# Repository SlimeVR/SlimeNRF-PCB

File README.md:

## notes

You need a segger jlink programmer to use this, USB dfu does not come with the initial bootloader of isp, and nrf52832 has no USB connectivity. nRF52840-dk development kit can be used, and also can double as a dongle for the trackers.

# slimenrf r3

Revision 3

E73-2G4M08S1C (nrf52840), icm42688 or compatible, mmc5983ma

https://oshwlab.com/sctanf/slimenrf3

# slimenrfaux2

Revision 2

isp1507-ax (nrf52832), icm42688 or compatible, mmc5983ma

* Uses nrf52832, no USB, SWD pins on dock connector instead
* No 0201 parts
* Removed onboard charger
* LED is brighter (sink instead of source)

pcb|3d
--|--
|

pcb before reflow|pcb with battery|tracker and case ()
--|--|--
||

# slimenrfauxaux2

Revision 2

icm42688 or compatible, mmc5983ma

pcb|3d
--|--
|

# slimenrfaux

Revision 1

isp1807-lr (nrf52840), icm42688 or compatible, mmc5983ma

* USB untested
* 0201 components are hard to solder
* Charger is hard to solder
* LED with default resistor is too dim

pcb|3d
--|--
|

finished pcb|pcb with battery|completed tracker (case: )
--|--|--
||

# slimenrfauxaux

Revision 1

icm42688 or compatible, mmc5983ma

* 0201 components are hard to solder

pcb|3d
--|--
|

# slimenrfdock

dock test pcb

charging for 8 devices at 300mA, max power draw 2.4A

* Gets pretty hot if all 8 chargers are in use but it works fine

pcb|3d
--|--
|

completed charger pcb|charging dock ()
--|--
|

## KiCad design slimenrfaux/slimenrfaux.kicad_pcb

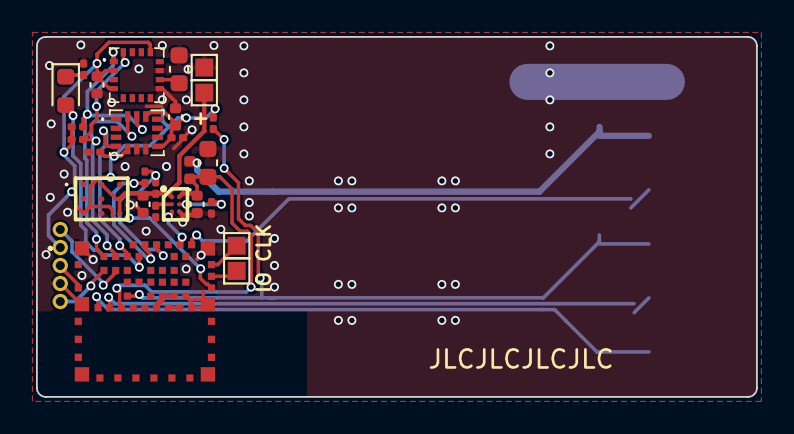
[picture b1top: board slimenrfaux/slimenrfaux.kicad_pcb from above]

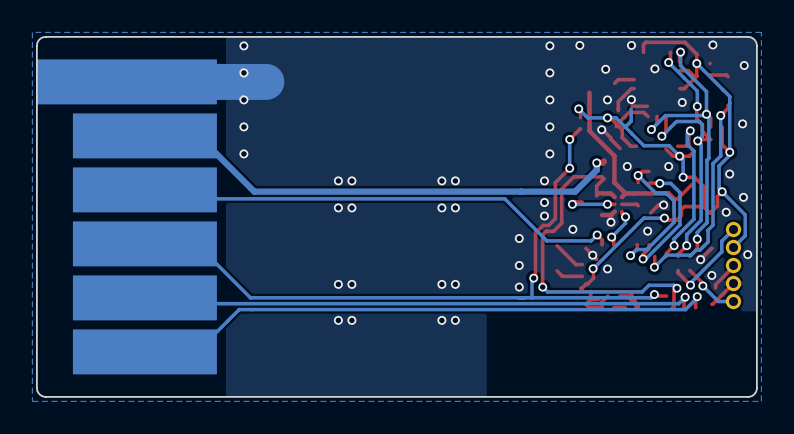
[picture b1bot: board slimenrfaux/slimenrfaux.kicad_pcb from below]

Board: 2 copper layers, 40.0 x 20.0 mm, 34 parts (6 on the bottom side), 26 nets.

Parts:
AC2: ICM-42688-V; IIM42352
C3, C4, C12: 1uF; C_0402_1005Metric
C8: 4.7uF; C_0603_1608Metric
C9: 10nF; C_0201_0603Metric
C10: 0.1uF; C_0201_0603Metric
C11: 2.2uF; C_0402_1005Metric
C13: 10uF; C_0603_1608Metric
D1: LED; LED_0603_1608Metric
D2: D; D_0402_1005Metric
IC1: ISP1807-LR-RS; ISP1807LRRS
IC2: BQ25101YFPR; BGA6C40P2X3_88X158X50
IC3: MMC5983MA
J1: Conn_01x05_Male; PinHeader_1x05_P1.00mm_Horizontal
PS1: TPS82740ASIPR
R1, R10: 10K; R_0201_0603Metric
R2: 540; R_0201_0603Metric
R4, R5: 2.7K; R_0201_0603Metric
R7: 1M; R_0201_0603Metric
R8: 510K; R_0201_0603Metric
R9: 10; R_0201_0603Metric
TP1, TP2, TP3, TP4, TP5, TP6, TP7, TP8, TP9, TP10: TestPoint; TestPoint_Pad_1.0x1.0mm

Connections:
ADCBAT: IC1.38 (P0_03_AIN1), R7.2, R8.1
ADCBATEN: IC1.40 (P0_02_AIN0), R8.2
CHGSTAT: IC1.34 (P0_06), IC2.C1 (~CHG)
D+: IC1.8 (D+), TP8.1
D-: IC1.10 (D-), TP7.1
Dock: IC1.32 (P0_08), TP5.1
GND: AC2.1 (AP_SDO_/_AP_AD0), AC2.6 (GND), AC2.7 (RESV_3), AC2.9 (INT2_/_FSYNC_/_CLKIN), C3.1, C4.2, C8.2, C9.2, C10.2, C11.2, C12.2, C13.2, IC1.1 (VSS_1), IC1.7 (VSS_2), IC1.14 (VSS_3), IC1.16 (VSS_4), IC1.18 (VSS_5), IC1.19 (P0_24), IC1.21 (VSS_6), IC1.23 (VSS_7), IC1.24 (VSS_8), IC1.25 (VSS_9), IC1.31 (VSS_10), IC2.C2 (VSS), IC3.9 (GND_1), IC3.11 (GND_2), J1.2, PS1.A1 (VSEL3), PS1.A3 (VSEL1), PS1.C2 (GND), R1.1, R2.2, R9.2, TP2.1, TP3.1
INT: AC2.4 (INT1_/_INT), IC1.43 (P0_11_TRACEDATA2)
INT2: IC1.6 (P0_26), J1.3
LED: D1.2 (A), IC1.41 (P0_25)
unnamed: C13.1, IC3.10 (CAP)
unnamed: D2.2 (A), TP4.1
unnamed: IC1.20 (OUT_ANT), IC1.22 (OUT_MOD)
unnamed: IC2.B1 (TS), R1.2
unnamed: IC2.B2 (ISET), R2.1
unnamed: D1.1 (K), R9.1
RST: IC1.13 (P0_18_RESET), R10.2, TP6.1
SCL: AC2.13 (AP_SCL_/_AP_SCLK), IC1.47 (P0_23), IC3.1 (SCL/SPI_SCK), R5.2
SCLAUX: IC1.56 (P1_09_TRACEDATA3), J1.1
SDA: AC2.14 (AP_SDA_/_AP_SDIO_/_AP_SDI), IC1.45 (P0_19), IC3.16 (SDA/SPI_SDI), R4.2
SDAAUX: IC1.55 (P1_08), J1.5
SWDCLK: IC1.30 (SWDCLK), TP10.1
SWDIO: IC1.28 (SWDIO), TP9.1
VBAT: C3.2, IC2.A1 (OUT), PS1.A2 (VSEL2), PS1.B3 (EN), PS1.C3 (VIN), R7.1, TP1.1
VBUS: C4.1, C8.1, D2.1 (K), IC1.12 (VBUS), IC2.A2 (IN)
VDD: AC2.5 (VDDIO), AC2.8 (VDD), AC2.12 (AP_CS), C9.1, C10.1, C11.1, C12.1, IC1.26 (VCC_NRF), IC3.2 (VDD), IC3.4 (SPI_CS), IC3.13 (VDDIO), J1.4, PS1.C1 (VOUT), R4.1, R5.1, R10.1

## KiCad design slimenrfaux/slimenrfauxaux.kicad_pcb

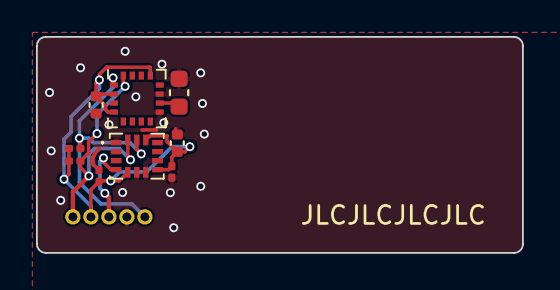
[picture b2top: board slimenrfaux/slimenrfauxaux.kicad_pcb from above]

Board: 2 copper layers, 27.0 x 12.0 mm, 10 parts (0 on the bottom side), 6 nets.

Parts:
AC2: ICM-42688-V; IIM42352
C9: 10nF; C_0201_0603Metric
C10: 0.1uF; C_0201_0603Metric
C11: 2.2uF; C_0402_1005Metric
C12: 1uF; C_0402_1005Metric
C13: 10uF; C_0603_1608Metric
J1: Conn_01x05_Male; PinHeader_1x05_P1.00mm_Horizontal
R4, R5: 2.2K; R_0201_0603Metric
U1: MMC5883MA; LGA-16_3x3mm_P0.5mm

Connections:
GND: AC2.1 (AP_SDO_/_AP_AD0), AC2.6 (GND), AC2.7 (RESV_3), AC2.9 (INT2_/_FSYNC_/_CLKIN), C9.2, C10.2, C11.2, C12.2, C13.2, J1.2, U1.9 (GND), U1.11 (GND)
INT: AC2.4 (INT1_/_INT), J1.3
unnamed: C13.1, U1.10 (CAP)
SCL: AC2.13 (AP_SCL_/_AP_SCLK), J1.1, R5.2, U1.1 (SCL)
SDA: AC2.14 (AP_SDA_/_AP_SDIO_/_AP_SDI), J1.5, R4.2, U1.16 (SDA)
VDD: AC2.5 (VDDIO), AC2.8 (VDD), AC2.12 (AP_CS), C9.1, C10.1, C11.1, C12.1, J1.4, R4.1, R5.1, U1.2 (VDD), U1.4 (NC), U1.13 (VDDIO)

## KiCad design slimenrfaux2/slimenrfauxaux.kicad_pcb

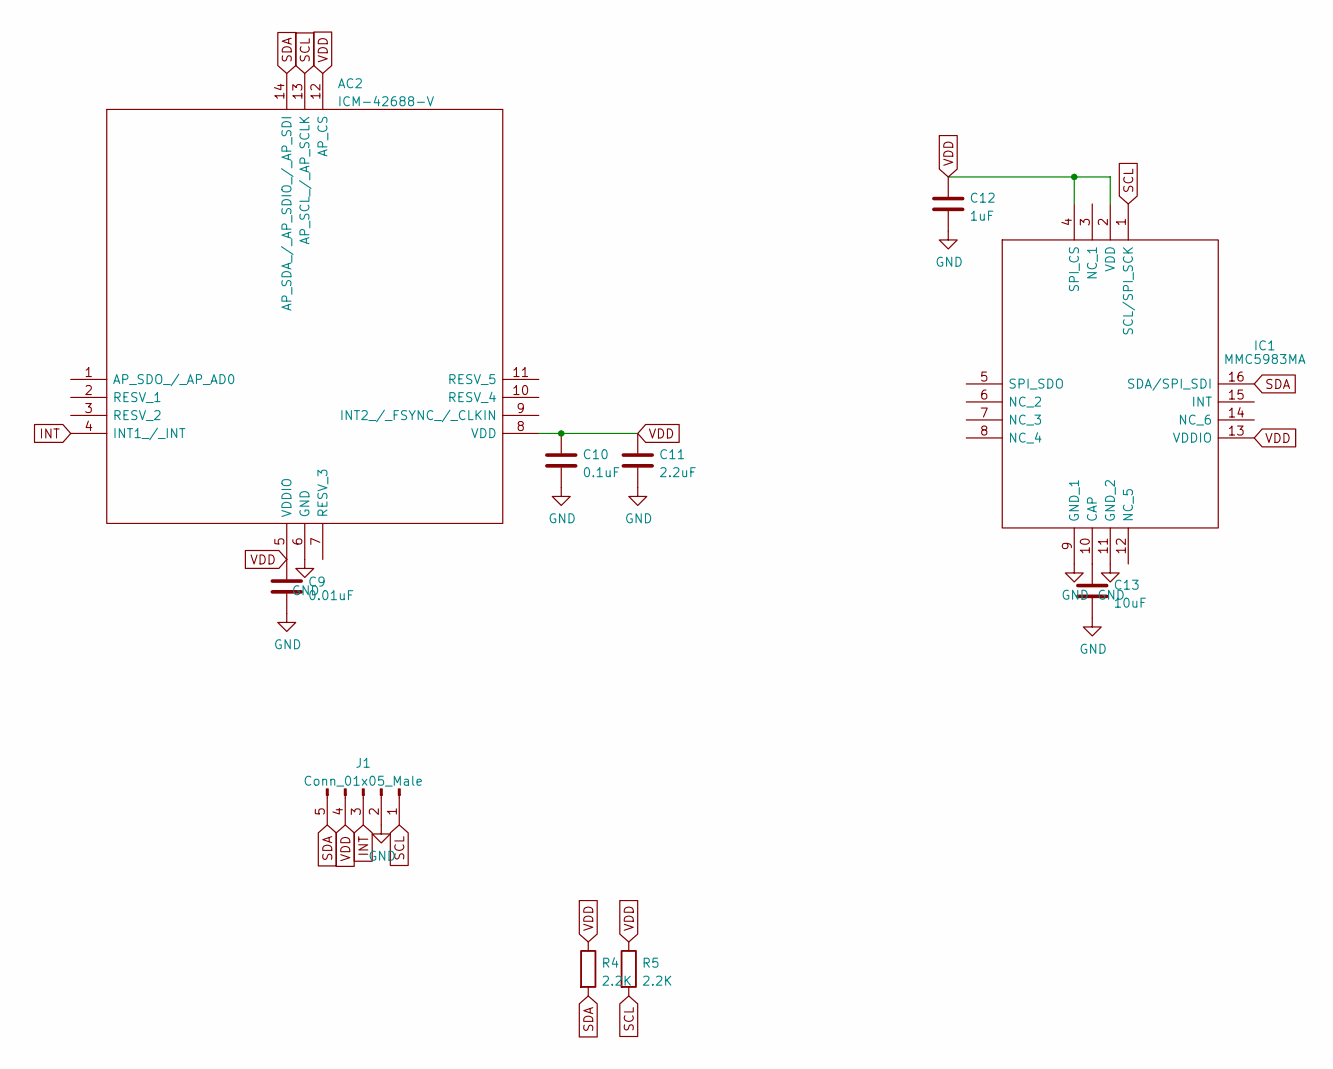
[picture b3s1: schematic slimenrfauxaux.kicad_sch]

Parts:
AC2: ICM-42688-V; IIM42352; Mouser Part Number 410-ICM-42688-V
C9: 0.01uF; C_0402_1005Metric
C10: 0.1uF; C_0402_1005Metric
C11: 2.2uF; C_0402_1005Metric
C12: 1uF; C_0402_1005Metric
C13: 10uF; C_0603_1608Metric
IC1: MMC5983MA; Mouser Part Number 438-MMC5983MA
J1: Conn_01x05_Male; PinHeader_1x05_P1.00mm_Horizontal
R4, R5: 2.2K; R_0402_1005Metric

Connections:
GND: AC2.6 (GND), C9.2, C10.2, C11.2, C12.2, C13.2, IC1.9 (GND_1), IC1.11 (GND_2), J1.2
INT: AC2.4 (INT1_/_INT), J1.3
unnamed: C13.1, IC1.10 (CAP)
SCL: AC2.13 (AP_SCL_/_AP_SCLK), IC1.1 (SCL/SPI_SCK), J1.1, R5.2
SDA: AC2.14 (AP_SDA_/_AP_SDIO_/_AP_SDI), IC1.16 (SDA/SPI_SDI), J1.5, R4.2
VDD: AC2.5 (VDDIO), AC2.8 (VDD), AC2.12 (AP_CS), C9.1, C10.1, C11.1, C12.1, IC1.2 (VDD), IC1.4 (SPI_CS), IC1.13 (VDDIO), J1.4, R4.1, R5.1

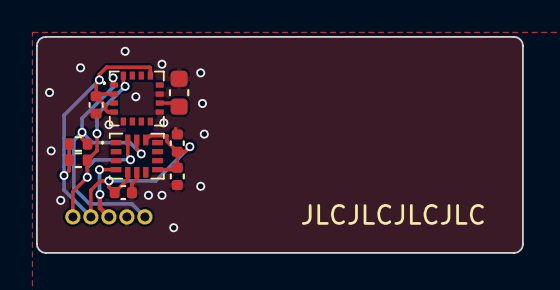
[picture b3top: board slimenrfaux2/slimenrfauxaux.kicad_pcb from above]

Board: 2 copper layers, 27.0 x 12.0 mm, 10 parts (0 on the bottom side), 6 nets.

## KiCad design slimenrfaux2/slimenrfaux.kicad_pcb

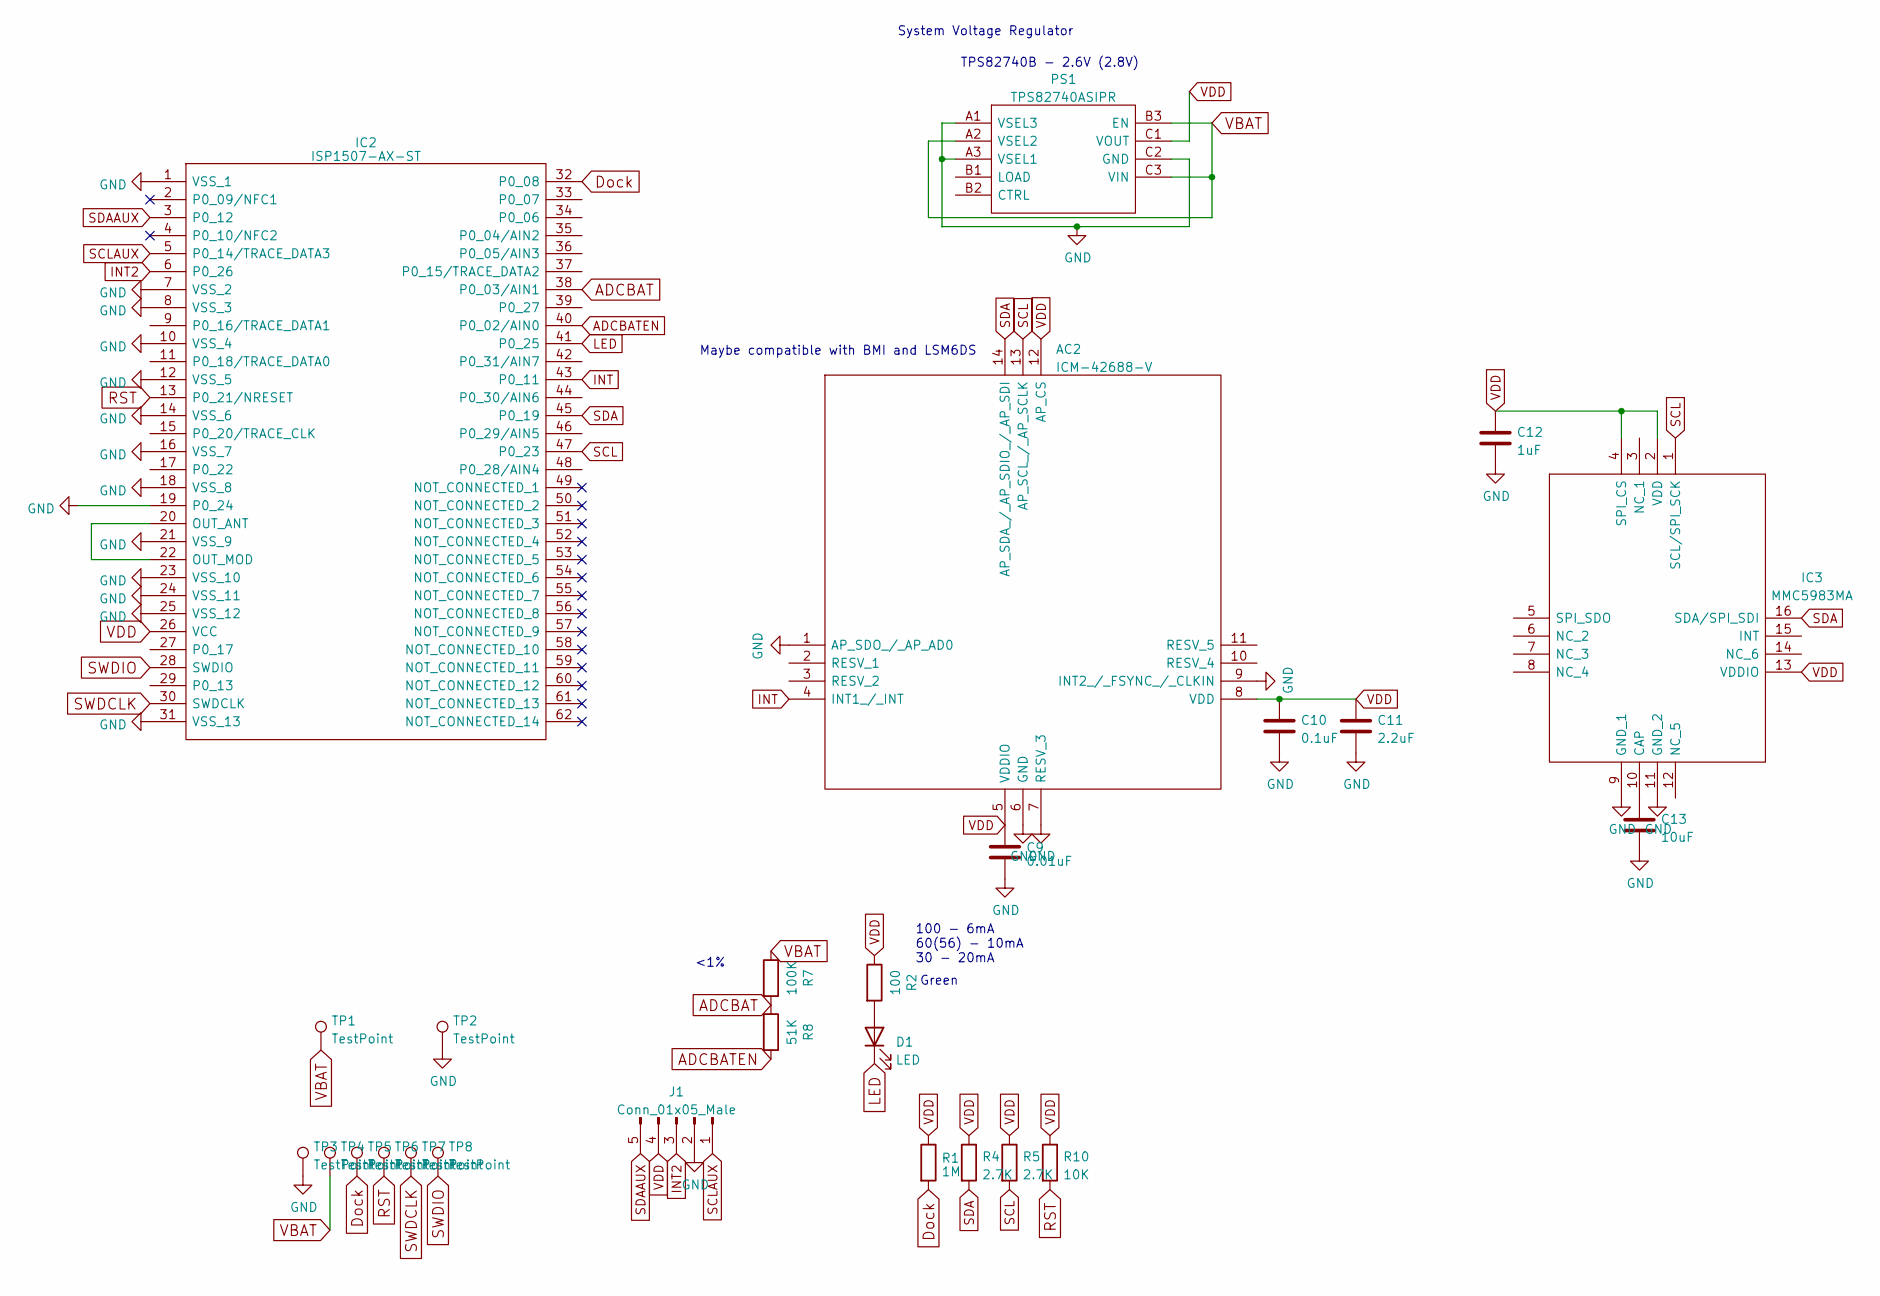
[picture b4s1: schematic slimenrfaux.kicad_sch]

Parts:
AC2: ICM-42688-V; IIM42352; Mouser Part Number 410-ICM-42688-V
C9: 0.01uF; C_0402_1005Metric
C10: 0.1uF; C_0402_1005Metric
C11: 2.2uF; C_0402_1005Metric
C12: 1uF; C_0402_1005Metric
C13: 10uF; C_0603_1608Metric
D1: LED; LED_0603_1608Metric
IC2: ISP1507-AX-ST; ISP1507AXST; Manufacturer_Part_Number ISP1507-AX-ST; Mouser Part Number 359-ISP1507-AX-ST
IC3: MMC5983MA; Mouser Part Number 438-MMC5983MA
J1: Conn_01x05_Male; PinHeader_1x05_P1.00mm_Horizontal
PS1: TPS82740ASIPR; Mouser Part Number 595-TPS82740ASIPR
R1: 1M; R_0402_1005Metric
R2: 100; R_0402_1005Metric
R4, R5: 2.7K; R_0402_1005Metric
R7: 100K; R_0402_1005Metric
R8: 51K; R_0402_1005Metric
R10: 10K; R_0402_1005Metric
TP1, TP2, TP3, TP4, TP5, TP6, TP7, TP8: TestPoint; TestPoint_Pad_1.0x1.0mm

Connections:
ADCBAT: IC2.38 (P0_03/AIN1), R7.2, R8.1
ADCBATEN: IC2.40 (P0_02/AIN0), R8.2
Dock: IC2.32 (P0_08), R1.2, TP5.1
GND: AC2.1 (AP_SDO_/_AP_AD0), AC2.6 (GND), AC2.7 (RESV_3), AC2.9 (INT2_/_FSYNC_/_CLKIN), C9.2, C10.2, C11.2, C12.2, C13.2, IC2.1 (VSS_1), IC2.7 (VSS_2), IC2.8 (VSS_3), IC2.10 (VSS_4), IC2.12 (VSS_5), IC2.14 (VSS_6), IC2.16 (VSS_7), IC2.18 (VSS_8), IC2.19 (P0_24), IC2.21 (VSS_9), IC2.23 (VSS_10), IC2.24 (VSS_11), IC2.25 (VSS_12), IC2.31 (VSS_13), IC3.9 (GND_1), IC3.11 (GND_2), J1.2, PS1.A1 (VSEL3), PS1.A3 (VSEL1), PS1.C2 (GND), TP2.1, TP3.1
INT: AC2.4 (INT1_/_INT), IC2.43 (P0_11)
INT2: IC2.6 (P0_26), J1.3
LED: D1.1 (K), IC2.41 (P0_25)
unnamed: D1.2 (A), R2.2
unnamed: IC2.20 (OUT_ANT), IC2.22 (OUT_MOD)
unnamed: C13.1, IC3.10 (CAP)
RST: IC2.13 (P0_21/NRESET), R10.2, TP6.1
SCL: AC2.13 (AP_SCL_/_AP_SCLK), IC2.47 (P0_23), IC3.1 (SCL/SPI_SCK), R5.2
SCLAUX: IC2.5 (P0_14/TRACE_DATA3), J1.1
SDA: AC2.14 (AP_SDA_/_AP_SDIO_/_AP_SDI), IC2.45 (P0_19), IC3.16 (SDA/SPI_SDI), R4.2
SDAAUX: IC2.3 (P0_12), J1.5
SWDCLK: IC2.30 (SWDCLK), TP7.1
SWDIO: IC2.28 (SWDIO), TP8.1
VBAT: PS1.A2 (VSEL2), PS1.B3 (EN), PS1.C3 (VIN), R7.1, TP1.1, TP4.1
VDD: AC2.5 (VDDIO), AC2.8 (VDD), AC2.12 (AP_CS), C9.1, C10.1, C11.1, C12.1, IC2.26 (VCC), IC3.2 (VDD), IC3.4 (SPI_CS), IC3.13 (VDDIO), J1.4, PS1.C1 (VOUT), R1.1, R2.1, R4.1, R5.1, R10.1

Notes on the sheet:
System Voltage Regulator
TPS82740B - 2.6V (2.8V)
Green
100 - 6mA 60(56) - 10mA 30 - 20mA
Maybe compatible with BMI and LSM6DS
<1%

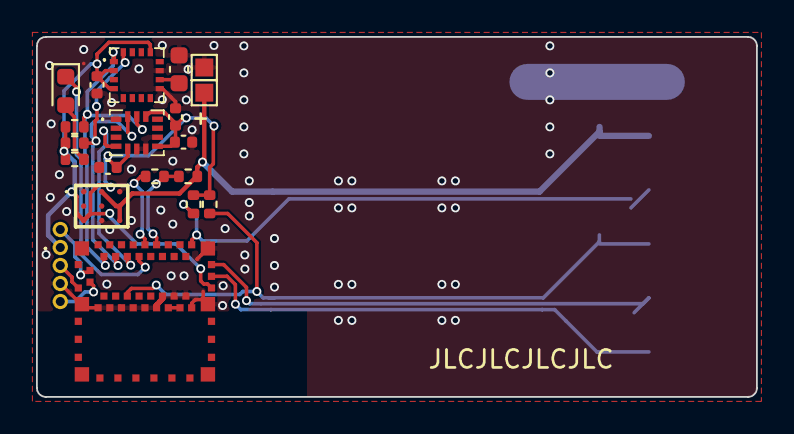
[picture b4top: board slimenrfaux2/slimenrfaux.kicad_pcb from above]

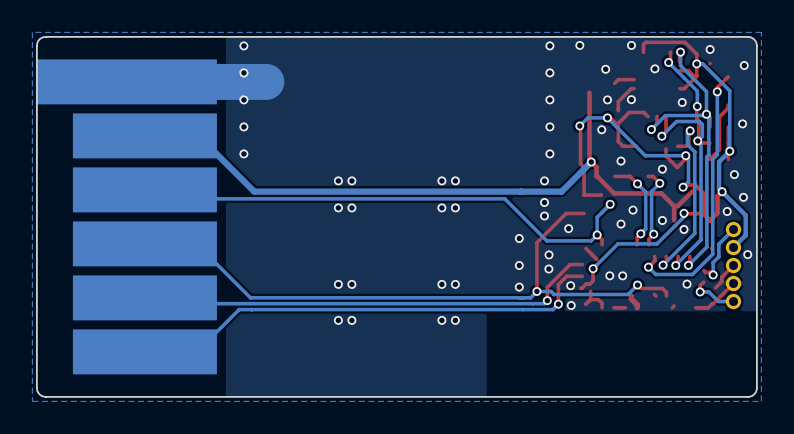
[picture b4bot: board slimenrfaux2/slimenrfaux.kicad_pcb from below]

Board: 2 copper layers, 40.0 x 20.0 mm, 26 parts (6 on the bottom side), 19 nets.

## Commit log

2023-04-19 add dock pcb
2023-04-19 add recent tracker pcbs
2023-04-19 add older tracker pcbs
2023-04-19 ill add the pics later
2023-04-19 add images
2023-04-19 add short info and images
2023-04-19 add auxes
2023-04-21 add model files
2023-04-23 tested rev2
2024-01-04 add case with removed ext port
2024-01-04 add pictures of finished boards
2024-01-04 add image
2024-02-28 [ImgBot] Optimize images
    *Total -- 1,164.94kb -> 813.48kb (30.17%)
    /images/slimenrfdock.png -- 203.63kb -> 115.04kb (43.51%)
    /images/slimenrfaux.png -- 210.11kb -> 138.40kb (34.13%)
    /images/slimenrfaux2.png -- 189.94kb -> 127.88kb (32.67%)
    /images/slimenrfauxaux.png -- 56.97kb -> 38.95kb (31.63%)
    /images/slimenrfauxaux2.png -- 60.44kb -> 41.52kb (31.31%)
2024-08-24 add r3 board (link)
2024-10-20 add updated case model
2024-11-16 update case
    remove extended ledge which may dig into battery
